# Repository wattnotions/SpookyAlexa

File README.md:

# SpookyAlexa
Control software for an animatronic mask plugged into an Amazon Alexa

For explanation of this project visit http://www.wattnotions.com/spooky-alexa-mask-documentation/

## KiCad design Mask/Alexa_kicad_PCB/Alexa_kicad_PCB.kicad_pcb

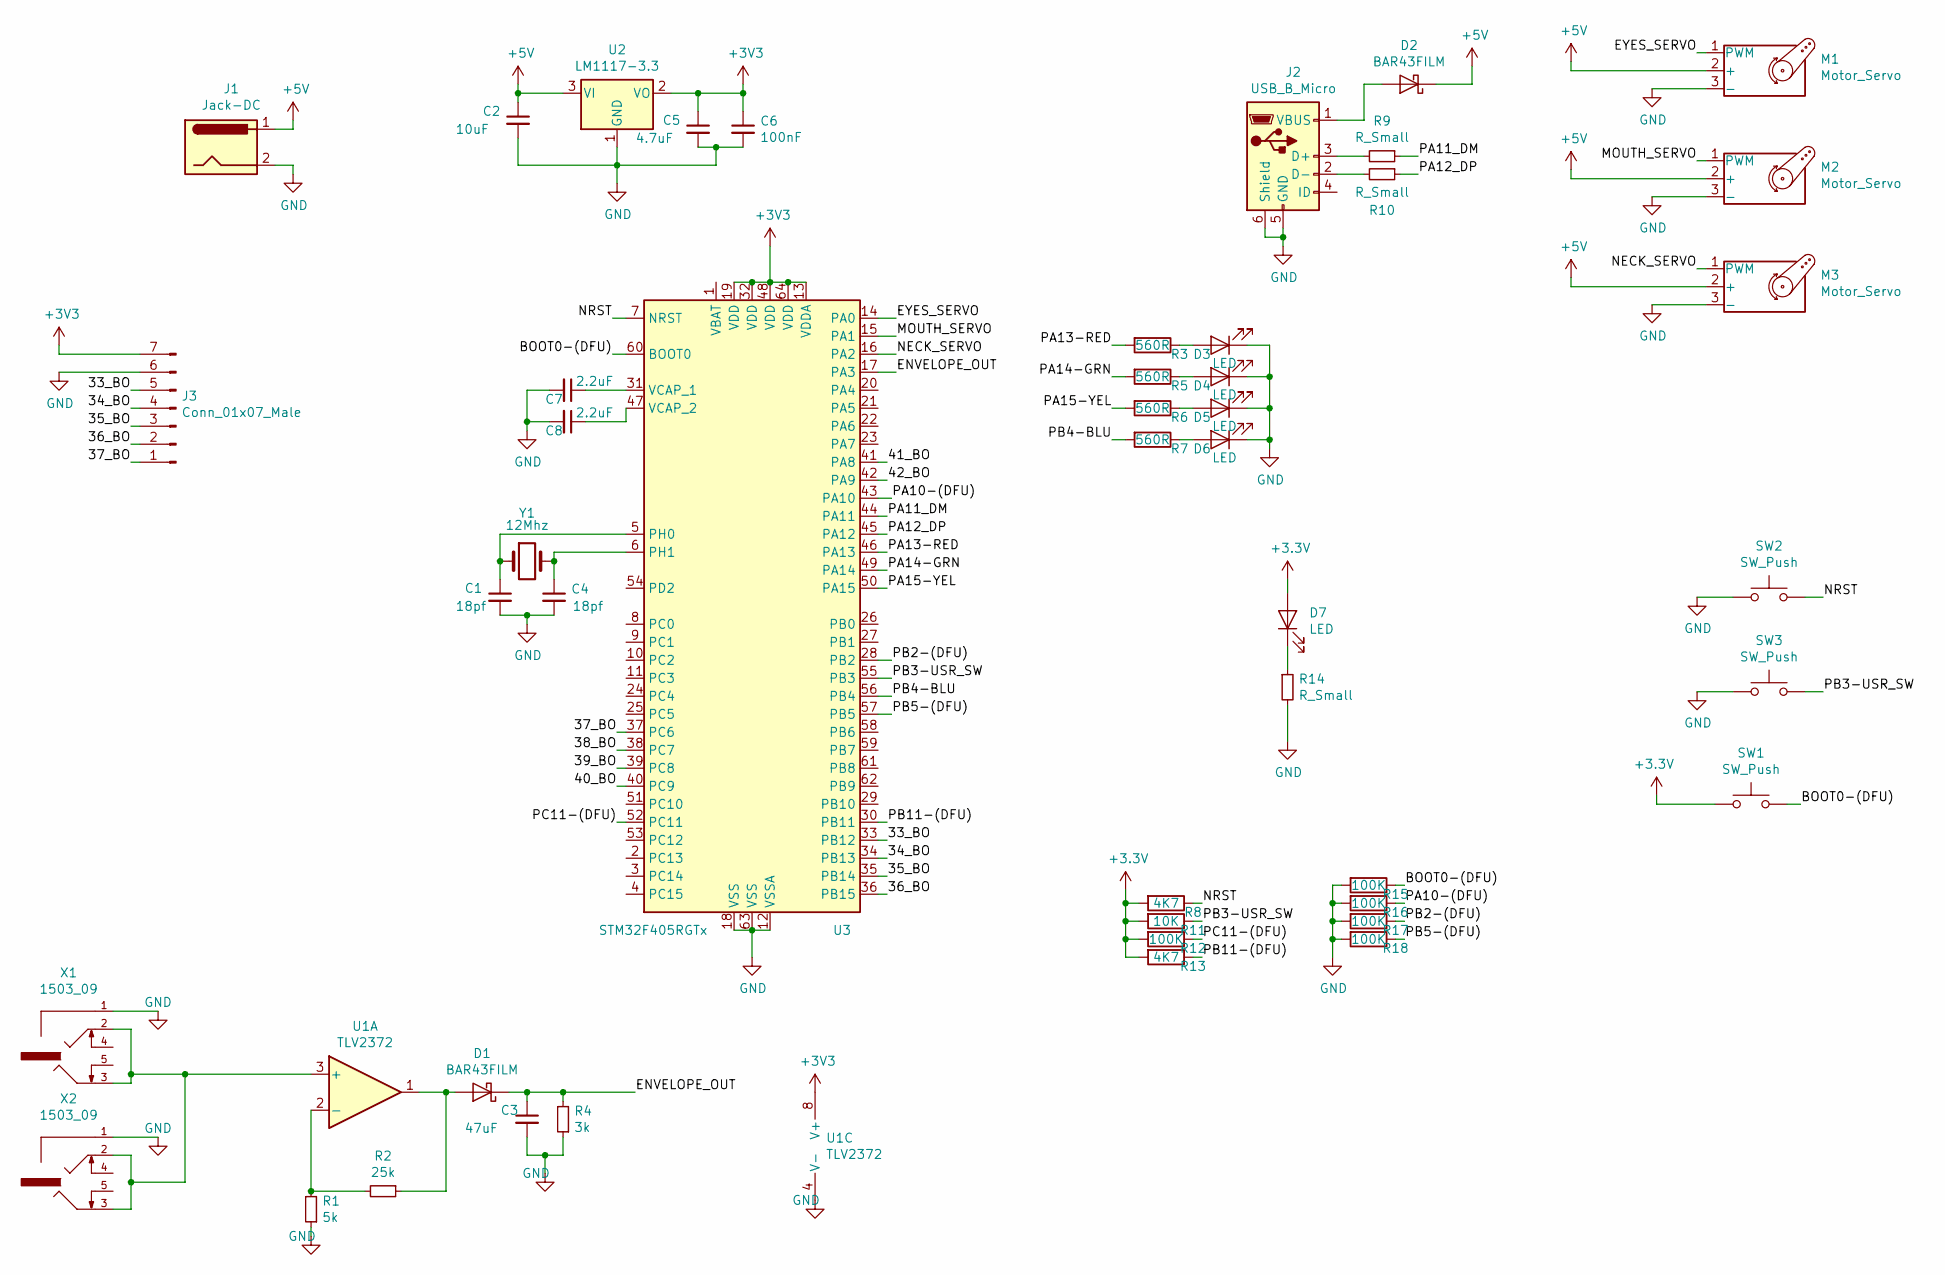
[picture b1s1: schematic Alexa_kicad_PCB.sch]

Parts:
C1, C4: 18pf; C_0603_1608Metric
C2: 10uF; C_0603_1608Metric
C3: 47uF; C_0603_1608Metric
C5: 4.7uF; C_0603_1608Metric
C6: 100nF; C_0603_1608Metric
C7, C8: 2.2uF; C_0603_1608Metric
D1, D2: BAR43FILM; SOT-23
D3, D4, D5, D6, D7: LED; LED_0603_1608Metric
J1: Jack-DC; BarrelJack_Wuerth_6941xx301002
J2: USB_B_Micro; USB_Micro-B_Molex-105017-0001
J3: Conn_01x07_Male; PinHeader_1x07_P2.54mm_Horizontal
M1, M2, M3: Motor_Servo; PinHeader_1x03_P2.54mm_Horizontal
R1: 5k; R_0603_1608Metric
R2: 25k; R_0603_1608Metric
R3, R5, R6, R7: 560R; R_0603_1608Metric
R4: 3k; R_0603_1608Metric
R8, R13: 4K7; R_0603_1608Metric
R9, R10, R14: R_Small; R_0603_1608Metric
R11: 10K; R_0603_1608Metric
R12, R15, R16, R17, R18: 100K; R_0603_1608Metric
SW1, SW2, SW3: SW_Push; SW_SPST_B3U-1000P
U1: TLV2372; SOIC-8_3.9x4.9mm_P1.27mm
U2: LM1117-3.3; SOT-223-3_TabPin2
U3: STM32F405RGTx; LQFP-64_10x10mm_P0.5mm
X1, X2: 1503_09
Y1: 12Mhz; Crystal_SMD_Abracon_ABM3-2Pin_5.0x3.2mm

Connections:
+5V: C2.1, D2.3 (K), J1.1, M1.2 (+), M2.2 (+), M3.2 (+), U2.3 (VI)
/33_BO: J3.5, U3.33 (PB12)
/34_BO: J3.4, U3.34 (PB13)
/35_BO: J3.3, U3.35 (PB14)
/36_BO: J3.2, U3.36 (PB15)
/37_BO: J3.1, U3.37 (PC6)
/38_BO: U3.38 (PC7)
/39_BO: U3.39 (PC8)
/40_BO: U3.40 (PC9)
/41_BO: U3.41 (PA8)
/42_BO: U3.42 (PA9)
/BOOT0-(DFU): R15.1, SW1.1, U3.60 (BOOT0)
/ENVELOPE_OUT: C3.1, D1.3 (K), R4.2, U3.17 (PA3)
/EYES_SERVO: M1.1 (PWM), U3.14 (PA0)
/MOUTH_SERVO: M2.1 (PWM), U3.15 (PA1)
/NECK_SERVO: M3.1 (PWM), U3.16 (PA2)
/NRST: R8.1, SW2.2, U3.7 (NRST)
/PA10-(DFU): R16.1, U3.43 (PA10)
/PA11_DM: R9.1, U3.44 (PA11)
/PA12_DP: R10.1, U3.45 (PA12)
/PA13-RED: R3.2, U3.46 (PA13)
/PA14-GRN: R5.2, U3.49 (PA14)
/PA15-YEL: R6.2, U3.50 (PA15)
/PB2-(DFU): R17.1, U3.28 (PB2)
/PB3-USR_SW: R11.1, SW3.2, U3.55 (PB3)
/PB4-BLU: R7.2, U3.56 (PB4)
/PB5-(DFU): R18.1, U3.57 (PB5)
/PB11-(DFU): R13.1, U3.30 (PB11)
/PC11-(DFU): R12.1, U3.52 (PC11)
GND: C1.2, C2.2, C3.2, C4.2, C5.2, C6.2, C7.2, C8.2, D3.1 (K), D4.1 (K), D5.1 (K), D6.1 (K), J1.2, J2.5 (GND), J2.6 (Shield), J3.6, M1.3 (-), M2.3 (-), M3.3 (-), R1.1, R4.1, R14.2, R15.2, R16.2, R17.2, R18.2, SW2.1, SW3.1, U1.4 (V-), U2.1 (GND), U3.12 (VSSA), U3.18 (VSS), U3.63 (VSS), X1.1, X2.1
unnamed: C1.1, U3.5 (PH0), Y1.1
unnamed: C4.1, U3.6 (PH1), Y1.2
unnamed: C7.1, U3.31 (VCAP_1)
unnamed: C8.1, U3.47 (VCAP_2)
unnamed: D1.1 (A), R2.1, U1.1
unnamed: D2.1 (A), J2.1 (VBUS)
unnamed: D3.2 (A), R3.1
unnamed: D4.2 (A), R5.1
unnamed: D5.2 (A), R6.1
unnamed: D6.2 (A), R7.1
unnamed: D7.1 (K), R14.1
unnamed: J2.2 (D-), R10.2
unnamed: J2.3 (D+), R9.2
unnamed: R1.2, R2.2, U1.2 (-)
unnamed: U1.3 (+), X1.2, X1.3, X2.2, X2.3

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
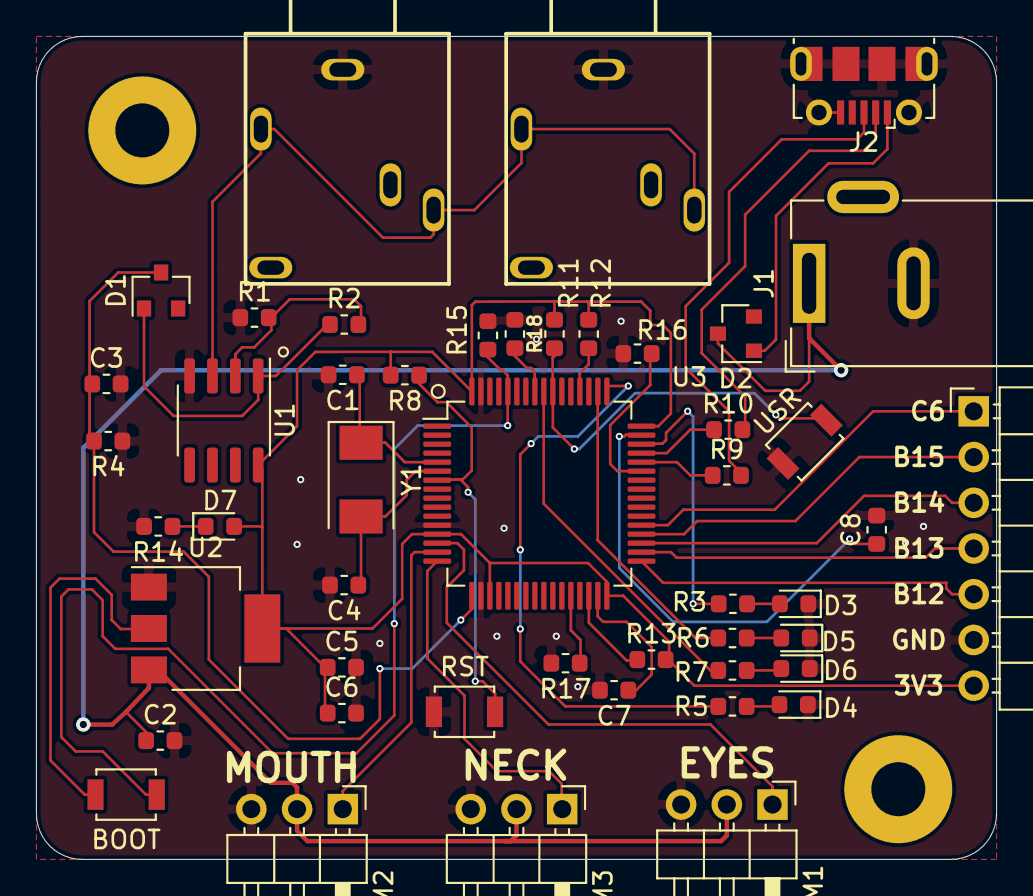
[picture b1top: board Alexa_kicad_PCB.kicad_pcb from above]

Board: 2 copper layers, 53.3 x 45.7 mm, 48 parts (0 on the bottom side), 41 nets.

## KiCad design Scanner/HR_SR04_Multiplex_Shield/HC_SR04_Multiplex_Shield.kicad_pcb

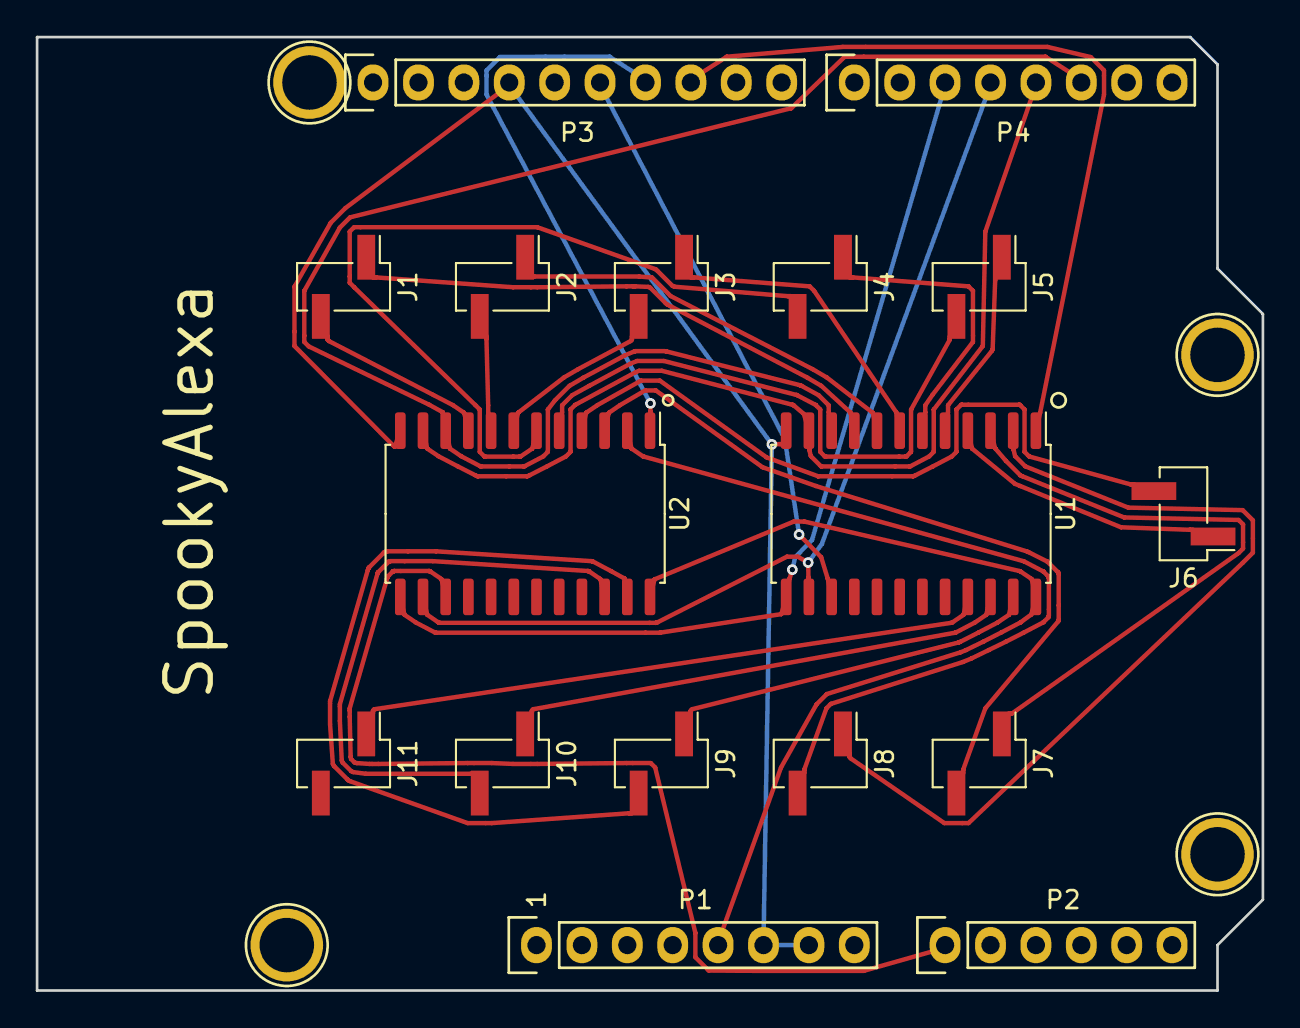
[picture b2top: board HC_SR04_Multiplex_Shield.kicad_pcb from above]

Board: 2 copper layers, 68.6 x 53.3 mm, 21 parts (0 on the bottom side), 31 nets.

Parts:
J1, J2, J3, J4, J5, J6, J7, J8, J9, J10, J11: Conn_01x02; PinHeader_1x02_P2.54mm_Vertical_SMD_Pin1Left
P1: Power; Socket_Strip_Arduino_1x08
P2: Analog; Socket_Strip_Arduino_1x06
P3: Digital; Socket_Strip_Arduino_1x10
P4: Digital; Socket_Strip_Arduino_1x08
P5, P6, P7, P8: CONN_01X01; Arduino_1pin
U1, U2: CD74HC4067M; SOIC-24W_7.5x15.4mm_P1.27mm

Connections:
+5V: P1.5, U1.24, U2.24
/2: P4.6, U1.10, U2.10
/3: P4.5, U1.11, U2.11
/4: P4.4, U1.14, U2.14
/5: P4.3, U1.13, U2.13
/10(ECHO): P3.8, U1.1
/11(TRIG): P3.7, U2.1
/12: P3.6, U1.15
/A0: P2.1, U2.15
/E1: J1.1, U1.9
/E2: J2.1, U1.8
/E3: J3.1, U1.7
/E4: J4.1, U1.6
/E5: J5.1, U1.5
/E6: J6.1, U1.4
/E7: J7.1, U1.3
/E8: J8.1, U1.2
/E9: J9.1, U1.23
/E10: J10.1, U1.22
/E11: J11.1, U1.21
/T1: J1.2, U2.9
/T2: J2.2, U2.8
/T3: J3.2, U2.7
/T4: J4.2, U2.6
/T5: J5.2, U2.5
/T6: J6.2, U2.4
/T7: J7.2, U2.3
/T8: J8.2, U2.2
/T9: J9.2, U2.23
/T10: J10.2, U2.22
GND: P1.6, P1.7, P3.4, U1.12, U2.12

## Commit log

2019-11-16 got gpio toggle working D2-d8, a1-15
2019-11-28 completed schematic of board
2019-11-28 export spectra file for topor import
2019-11-28 flipped components to make usb access easier
2019-11-28 fixed unconnected nets
2019-11-28 exported topor autoroute, still needs some work
2019-12-02 routed and ready for manufacture
2019-12-02 added "SpookyAlexa" silk text
2019-12-02 removed ground plane bcuz it looks cooler
2020-01-11 added working example
2020-01-12 got binary port count working
2020-01-17 got main sensor read loop working
2020-01-17 added printSensorVals function
2020-01-17 added selectSensor function
2020-01-17 added NUM_SENSORS def
2020-01-17 got rough location tracking working
2020-03-10 added datasheet for esp32
2020-03-27 got angle calc in degrees working
2020-03-27 added 180 degree line plots
2020-06-09 stated kicad pcb design
2020-06-09 added arduino nano schematic
2020-06-09 changed dir structure
2020-06-09 changed dir name
2020-06-09 last working version from video
2020-07-04 started schematic
2020-07-05 schematic progressed 20% completed
2020-07-11 started audio section of schematic
2020-07-16 finished analog schematic layout part
2020-07-29 changed op amp to tlv2372
2020-07-31 changed 3.5mm jack to 1503 09 part symbol
2020-08-03 all footprints matched to symbols
2020-08-03 started board layout
2020-08-03 footprints placed, ready for routing
2020-08-09 routing completed
2020-08-09 silkscreen text partially finished
2020-08-10 silk screen done, board finished
2020-09-09 cleaned up dfu pullups on schematic - added buttons
2020-09-09 added vcap caps
2020-09-09 added pwr + indication leds
2020-09-09 ADDED LABS NRST AND USR_SW
2020-09-16 v0.2 routing started
2020-09-17 v0.2 routing completed
2020-09-20 fixed missing envelope out trace
2020-09-20 ran DRC and fixed 2 issues
2020-09-20 cleaned up silk screen
2020-09-20 moved pin 0 ref for microcontroller
2020-09-21 changed c3 to 1206, generated jlcpcb fab files
